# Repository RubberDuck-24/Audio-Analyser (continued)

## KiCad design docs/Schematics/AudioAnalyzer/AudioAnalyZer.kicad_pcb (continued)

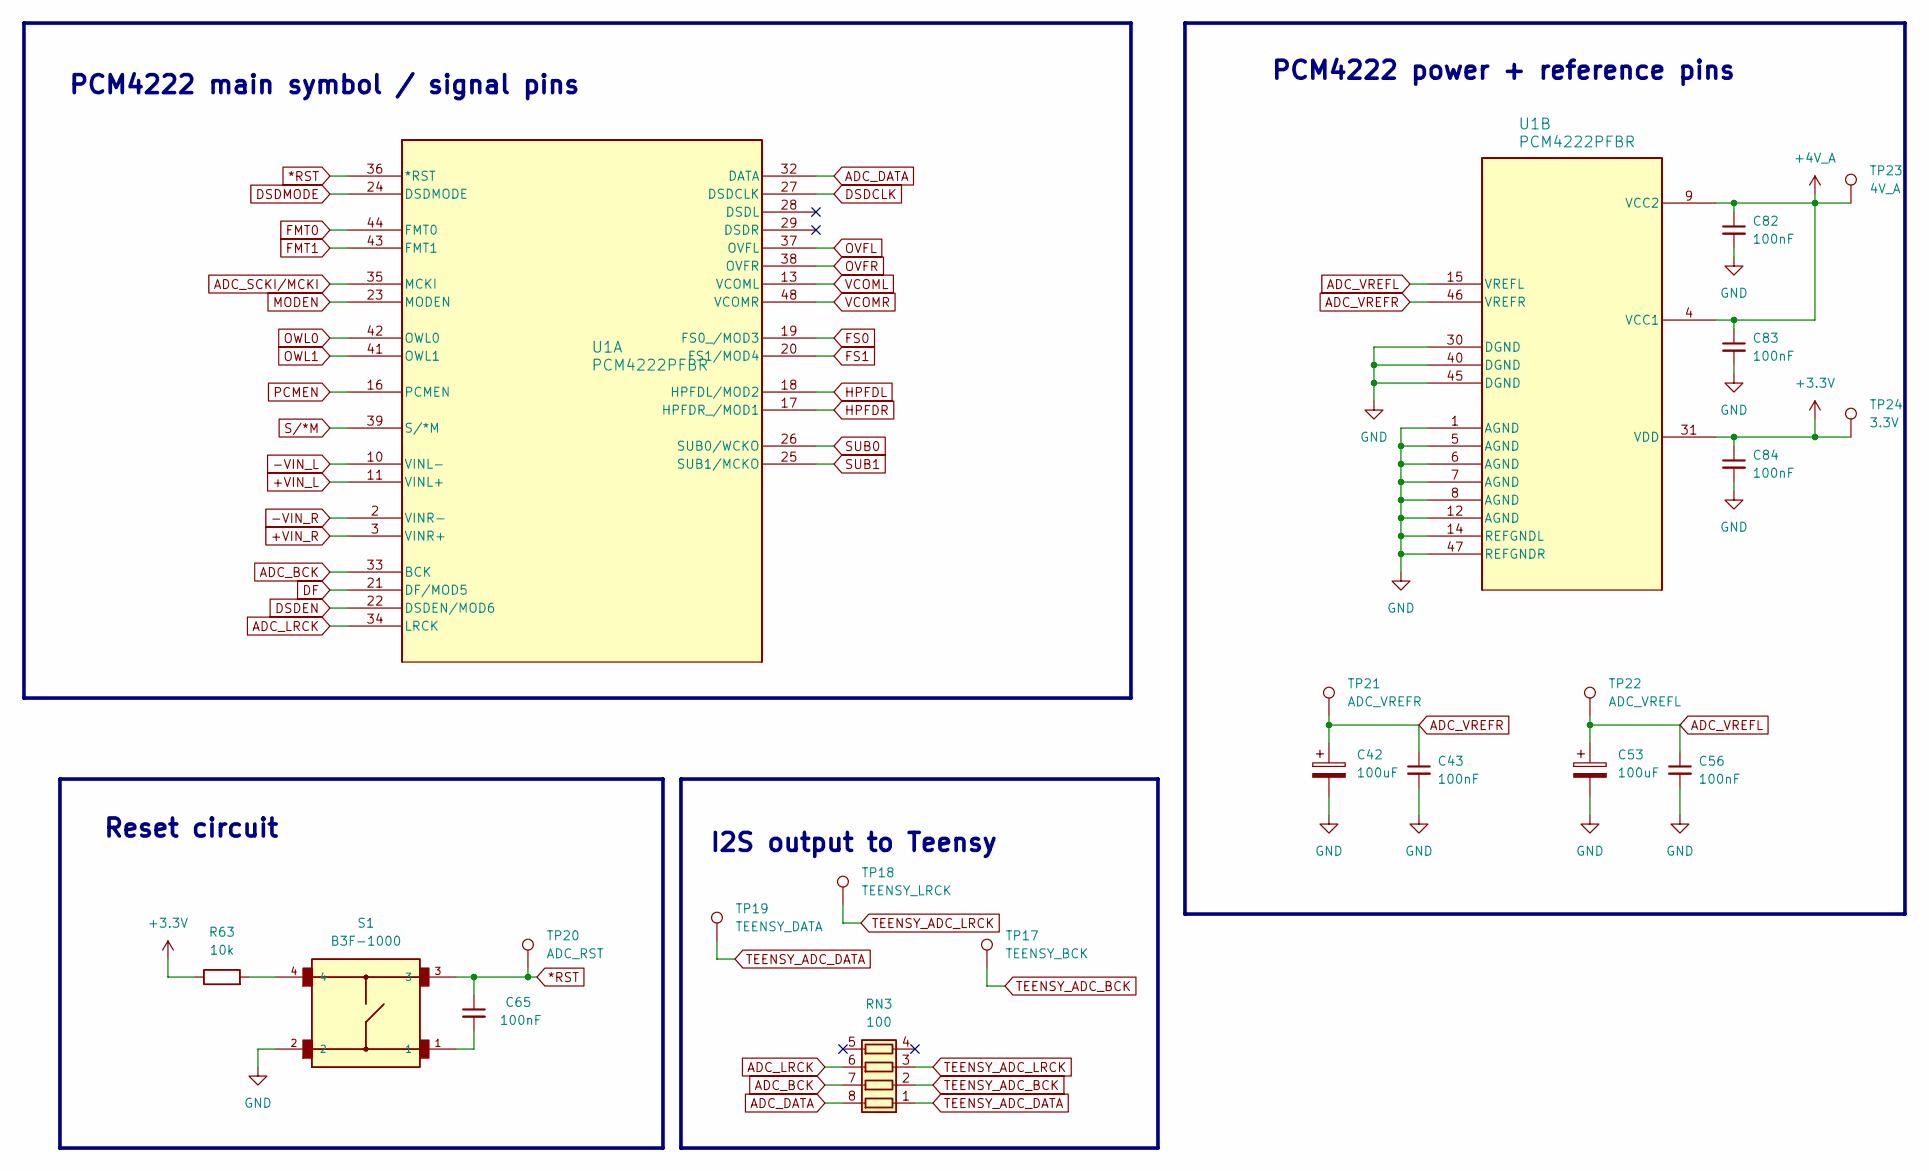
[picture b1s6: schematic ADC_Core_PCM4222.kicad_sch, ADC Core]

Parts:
C42, C53: 100uF; C_1210_3225Metric
C43, C56, C65, C82, C83, C84: 100nF; C_0603_1608Metric_Pad1.08x0.95mm_HandSolder
R63: 10k; R_0603_1608Metric_Pad0.98x0.95mm_HandSolder
RN3: 100; RESCAXS80P320X160X60-8N
S1: B3F-1000; SW_B3F-1000
TP17: TEENSY_BCK; TestPoint_Pad_D1.5mm
TP18: TEENSY_LRCK; TestPoint_Pad_D1.5mm
TP19: TEENSY_DATA; TestPoint_Pad_D1.5mm
TP20: ADC_RST; TestPoint_Pad_D1.5mm
TP21: ADC_VREFR; TestPoint_Pad_D1.5mm
TP22: ADC_VREFL; TestPoint_Pad_D1.5mm
TP23: 4V_A; TestPoint_Pad_D1.5mm
TP24: 3.3V; TestPoint_Pad_D1.5mm
U1: PCM4222PFBR; PFB48-M

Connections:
*RST: C65.1, S1.3, TP20.1 (1_1), U1.36 (*RST)
+3.3V: C84.1, R63.1, TP24.1 (1_1), U1.31 (VDD); also elsewhere on the board
+4V_A: C82.1, C83.1, TP23.1, U1.4 (VCC1), U1.9 (VCC2); also elsewhere on the board
+VIN_L: U1.11 (VINL+); also elsewhere on the board
+VIN_R: U1.3 (VINR+); also elsewhere on the board
-VIN_L: U1.10 (VINL-); also elsewhere on the board
-VIN_R: U1.2 (VINR-); also elsewhere on the board
ADC_BCK: RN3.7 (R2.2), U1.33 (BCK); also elsewhere on the board
ADC_DATA: RN3.8 (R1.2), U1.32 (DATA)
ADC_LRCK: RN3.6 (R3.2), U1.34 (LRCK); also elsewhere on the board
ADC_SCKI/MCKI: U1.35 (MCKI); also elsewhere on the board
ADC_VREFL: C53.1, C56.1, TP22.1 (1_1), U1.15 (VREFL)
ADC_VREFR: C42.1, C43.1, TP21.1 (1_1), U1.46 (VREFR)
DF: U1.21 (DF/MOD5); also elsewhere on the board
DSDCLK: U1.27 (DSDCLK)
DSDEN: U1.22 (DSDEN/MOD6); also elsewhere on the board
DSDMODE: U1.24 (DSDMODE); also elsewhere on the board
FMT0: U1.44 (FMT0); also elsewhere on the board
FMT1: U1.43 (FMT1); also elsewhere on the board
FS0: U1.19 (FS0_/MOD3); also elsewhere on the board
FS1: U1.20 (FS1/MOD4); also elsewhere on the board
GND: C42.2, C43.2, C53.2, C56.2, C82.2, C83.2, C84.2, S1.2, U1.1 (AGND), U1.5 (AGND), U1.6 (AGND), U1.7 (AGND), U1.8 (AGND), U1.12 (AGND), U1.14 (REFGNDL), U1.30 (DGND), U1.40 (DGND), U1.45 (DGND), U1.47 (REFGNDR); also elsewhere on the board
HPFDL: U1.17 (HPFDR_/MOD1), U1.18 (HPFDL/MOD2); also elsewhere on the board
MODEN: U1.23 (MODEN); also elsewhere on the board
unnamed: C65.2, S1.1
unnamed: R63.2, S1.4
OVFL: U1.37 (OVFL); also elsewhere on the board
OVFR: U1.38 (OVFR); also elsewhere on the board
OWL0: U1.42 (OWL0); also elsewhere on the board
OWL1: U1.41 (OWL1); also elsewhere on the board
PCMEN: U1.16 (PCMEN); also elsewhere on the board
SUB0: U1.26 (SUB0/WCKO); also elsewhere on the board
SUB1: U1.25 (SUB1/MCKO); also elsewhere on the board
S/*M: U1.39 (S/*M); also elsewhere on the board
TEENSY_ADC_BCK: RN3.2 (R2.1), TP17.1 (1_1); also elsewhere on the board
TEENSY_ADC_DATA: RN3.1 (R1.1), TP19.1 (1_1); also elsewhere on the board
TEENSY_ADC_LRCK: RN3.3 (R3.1), TP18.1 (1_1); also elsewhere on the board
VCOML: U1.13 (VCOML); also elsewhere on the board
VCOMR: U1.48 (VCOMR); also elsewhere on the board

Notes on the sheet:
PCM4222 main symbol / signal pins
I2S output to Teensy
PCM4222 power + reference pins
Reset circuit

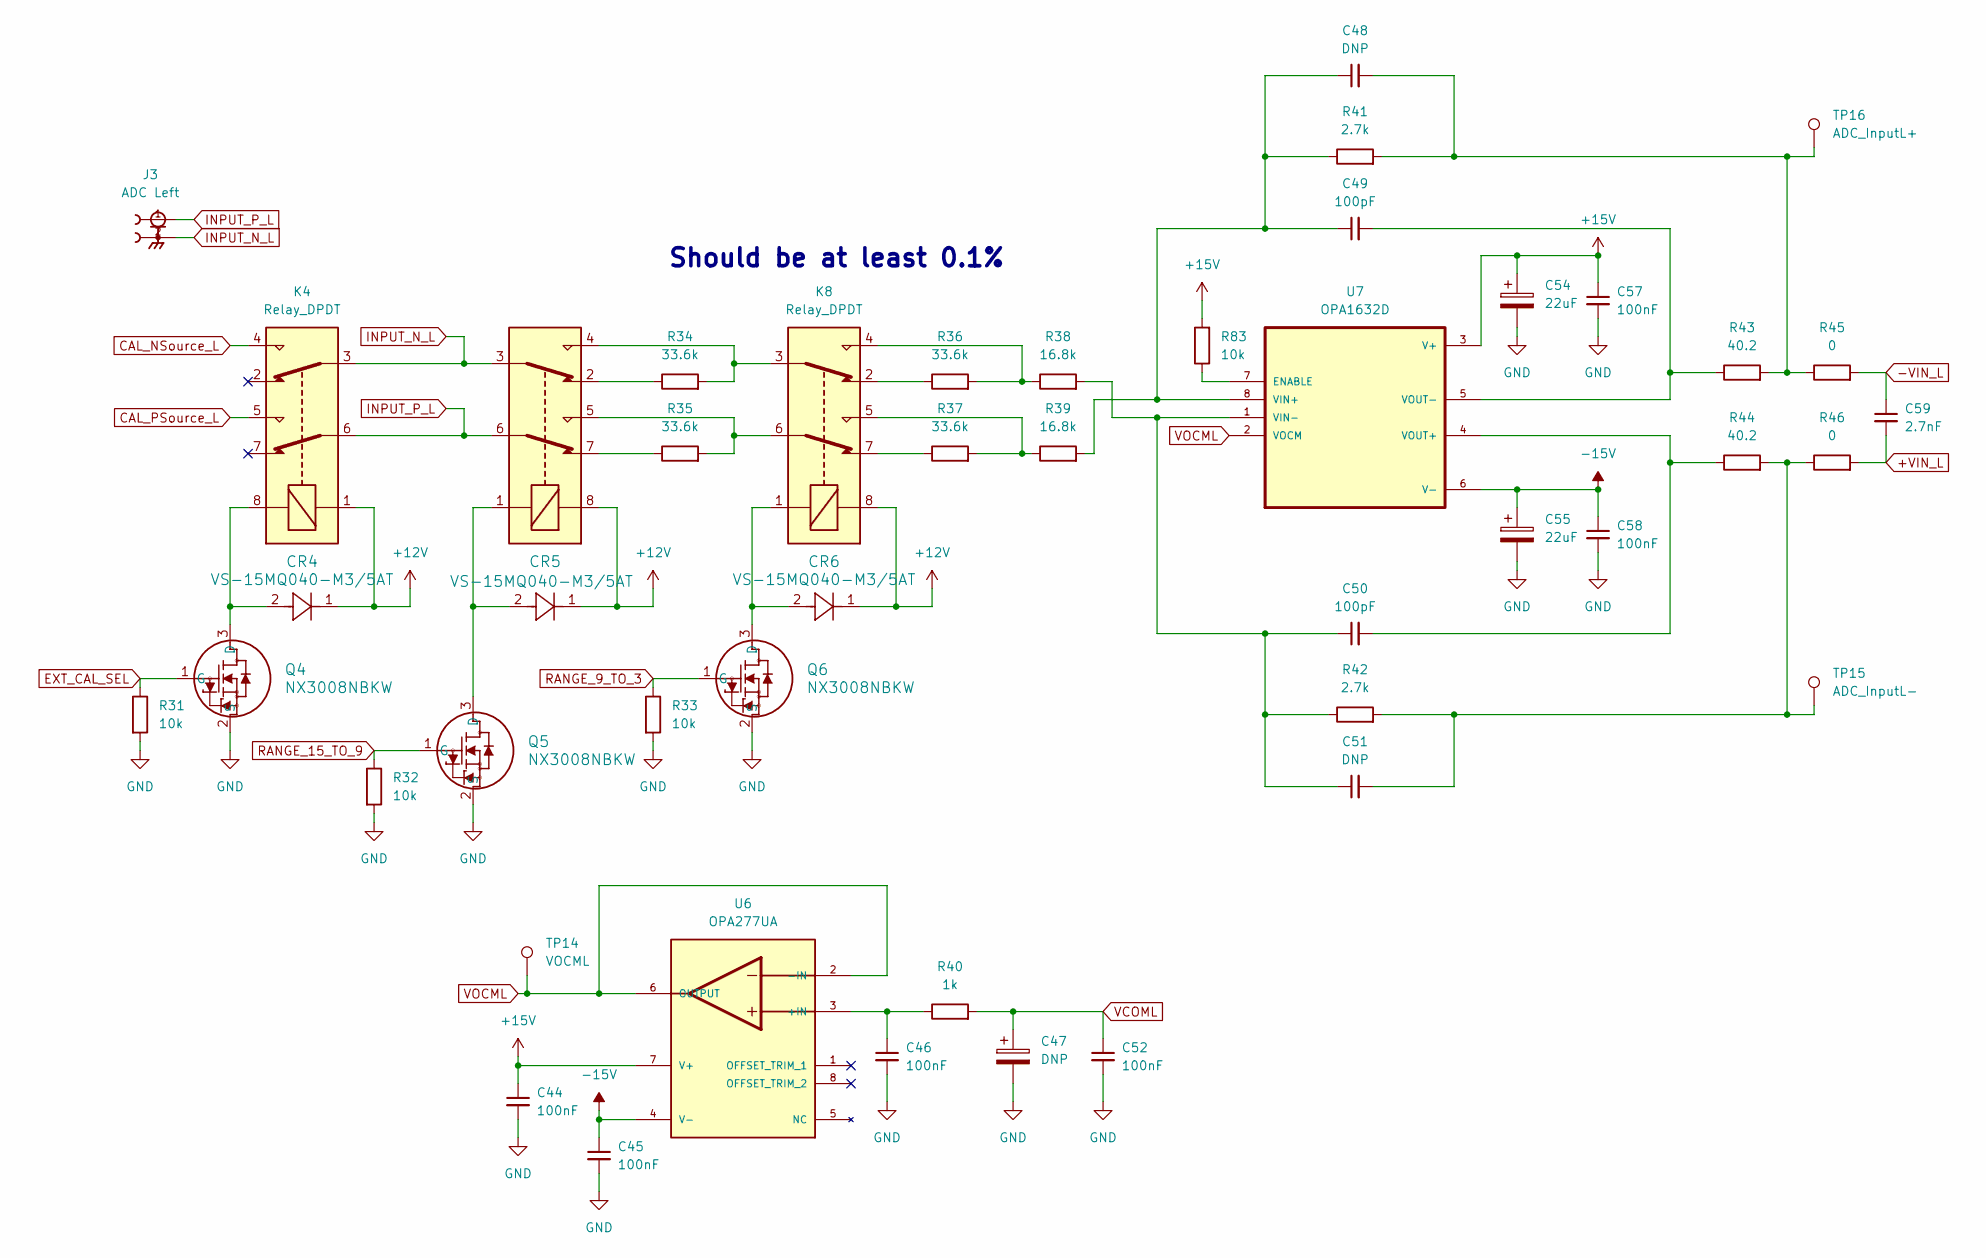
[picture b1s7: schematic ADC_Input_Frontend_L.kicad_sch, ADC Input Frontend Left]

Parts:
C44, C45, C46, C52, C57, C58: 100nF; C_0603_1608Metric_Pad1.08x0.95mm_HandSolder
C47, C48, C51: DNP; C_0603_1608Metric_Pad1.08x0.95mm_HandSolder
C49, C50: 100pF; C_0603_1608Metric_Pad1.08x0.95mm_HandSolder
C54, C55: 22uF; C_1206_3216Metric
C59: 2.7nF; C_0603_1608Metric_Pad1.08x0.95mm_HandSolder
CR4, CR5, CR6: VS-15MQ040-M3/5AT; CR_Q040-M3&slash_5AT_VIS
J3: ADC Left; LINX_CONBNC002
K4, K7, K8: Relay_DPDT; RELAY_IM06DGR
Q4, Q5, Q6: NX3008NBKW; SC-70_SOT323_NEX
R31, R32, R33, R83: 10k; R_0603_1608Metric_Pad0.98x0.95mm_HandSolder
R34, R35, R36, R37: 33.6k; R_0603_1608Metric_Pad0.98x0.95mm_HandSolder
R38, R39: 16.8k; R_0603_1608Metric_Pad0.98x0.95mm_HandSolder
R40: 1k; R_0603_1608Metric_Pad0.98x0.95mm_HandSolder
R41, R42: 2.7k; R_0603_1608Metric_Pad0.98x0.95mm_HandSolder
R43, R44: 40.2; R_0603_1608Metric_Pad0.98x0.95mm_HandSolder
R45, R46: 0; R_0603_1608Metric_Pad0.98x0.95mm_HandSolder
TP14: VOCML; TestPoint_Pad_D1.5mm
TP15: ADC_InputL-; TestPoint_Pad_D1.5mm
TP16: ADC_InputL+; TestPoint_Pad_D1.5mm
U6: OPA277UA; SOIC127P599X175-8N; PARTREV 02/2019
U7: OPA1632D; SOIC127P599X175-8N

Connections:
+12V: CR4.1, CR5.1, CR6.1, K4.1, K7.8, K8.8; also elsewhere on the board
+15V: C44.1, C54.1, C57.1, R83.2, U6.7 (V+), U7.3 (V+); also elsewhere on the board
+VIN_L: C59.2, R46.2; also elsewhere on the board
-15V: C45.1, C55.1, C58.1, U6.4 (V-), U7.6 (V-); also elsewhere on the board
-VIN_L: C59.1, R45.2; also elsewhere on the board
CAL_NSource_L: K4.4; also elsewhere on the board
CAL_PSource_L: K4.5; also elsewhere on the board
EXT_CAL_SEL: Q4.1 (G), R31.1; also elsewhere on the board
GND: C44.2, C45.2, C46.2, C47.2, C52.2, C54.2, C55.2, C57.2, C58.2, Q4.2 (S), Q5.2 (S), Q6.2 (S), R31.2, R32.2, R33.2; also elsewhere on the board
INPUT_N_L: J3.2, J3.S1, J3.S2, K4.3, K7.3
INPUT_P_L: J3.1, K4.6, K7.6
unnamed: C48.2, R41.2, R43.2, R45.1, TP16.1 (1_1)
unnamed: C51.2, R42.2, R44.2, R46.1, TP15.1 (1_1)
unnamed: K7.2, R34.1
unnamed: K7.4, K8.3, R34.2
unnamed: K7.5, K8.6, R35.2
unnamed: K7.7, R35.1
unnamed: K8.2, R36.1
unnamed: K8.4, R36.2, R38.1
unnamed: K8.5, R37.2, R39.1
unnamed: K8.7, R37.1
unnamed: CR4.2, K4.8, Q4.3 (D)
unnamed: CR5.2, K7.1, Q5.3 (D)
unnamed: CR6.2, K8.1, Q6.3 (D)
unnamed: C46.1, R40.1, U6.3 (+IN)
unnamed: R83.1, U7.7 (ENABLE)
unnamed: C48.1, C49.1, R39.2, R41.1, U7.8 (VIN+)
unnamed: C50.1, C51.1, R38.2, R42.1, U7.1 (VIN-)
unnamed: C50.2, R44.1, U7.4 (VOUT+)
unnamed: C49.2, R43.1, U7.5 (VOUT-)
RANGE_9_TO_3: Q6.1 (G), R33.1; also elsewhere on the board
RANGE_15_TO_9: Q5.1 (G), R32.1; also elsewhere on the board
VCOML: C47.1, C52.1, R40.2; also elsewhere on the board
VOCML: TP14.1 (1_1), U6.2 (-IN), U6.6 (OUTPUT), U7.2 (VOCM)

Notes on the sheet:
Should be at least 0.1%

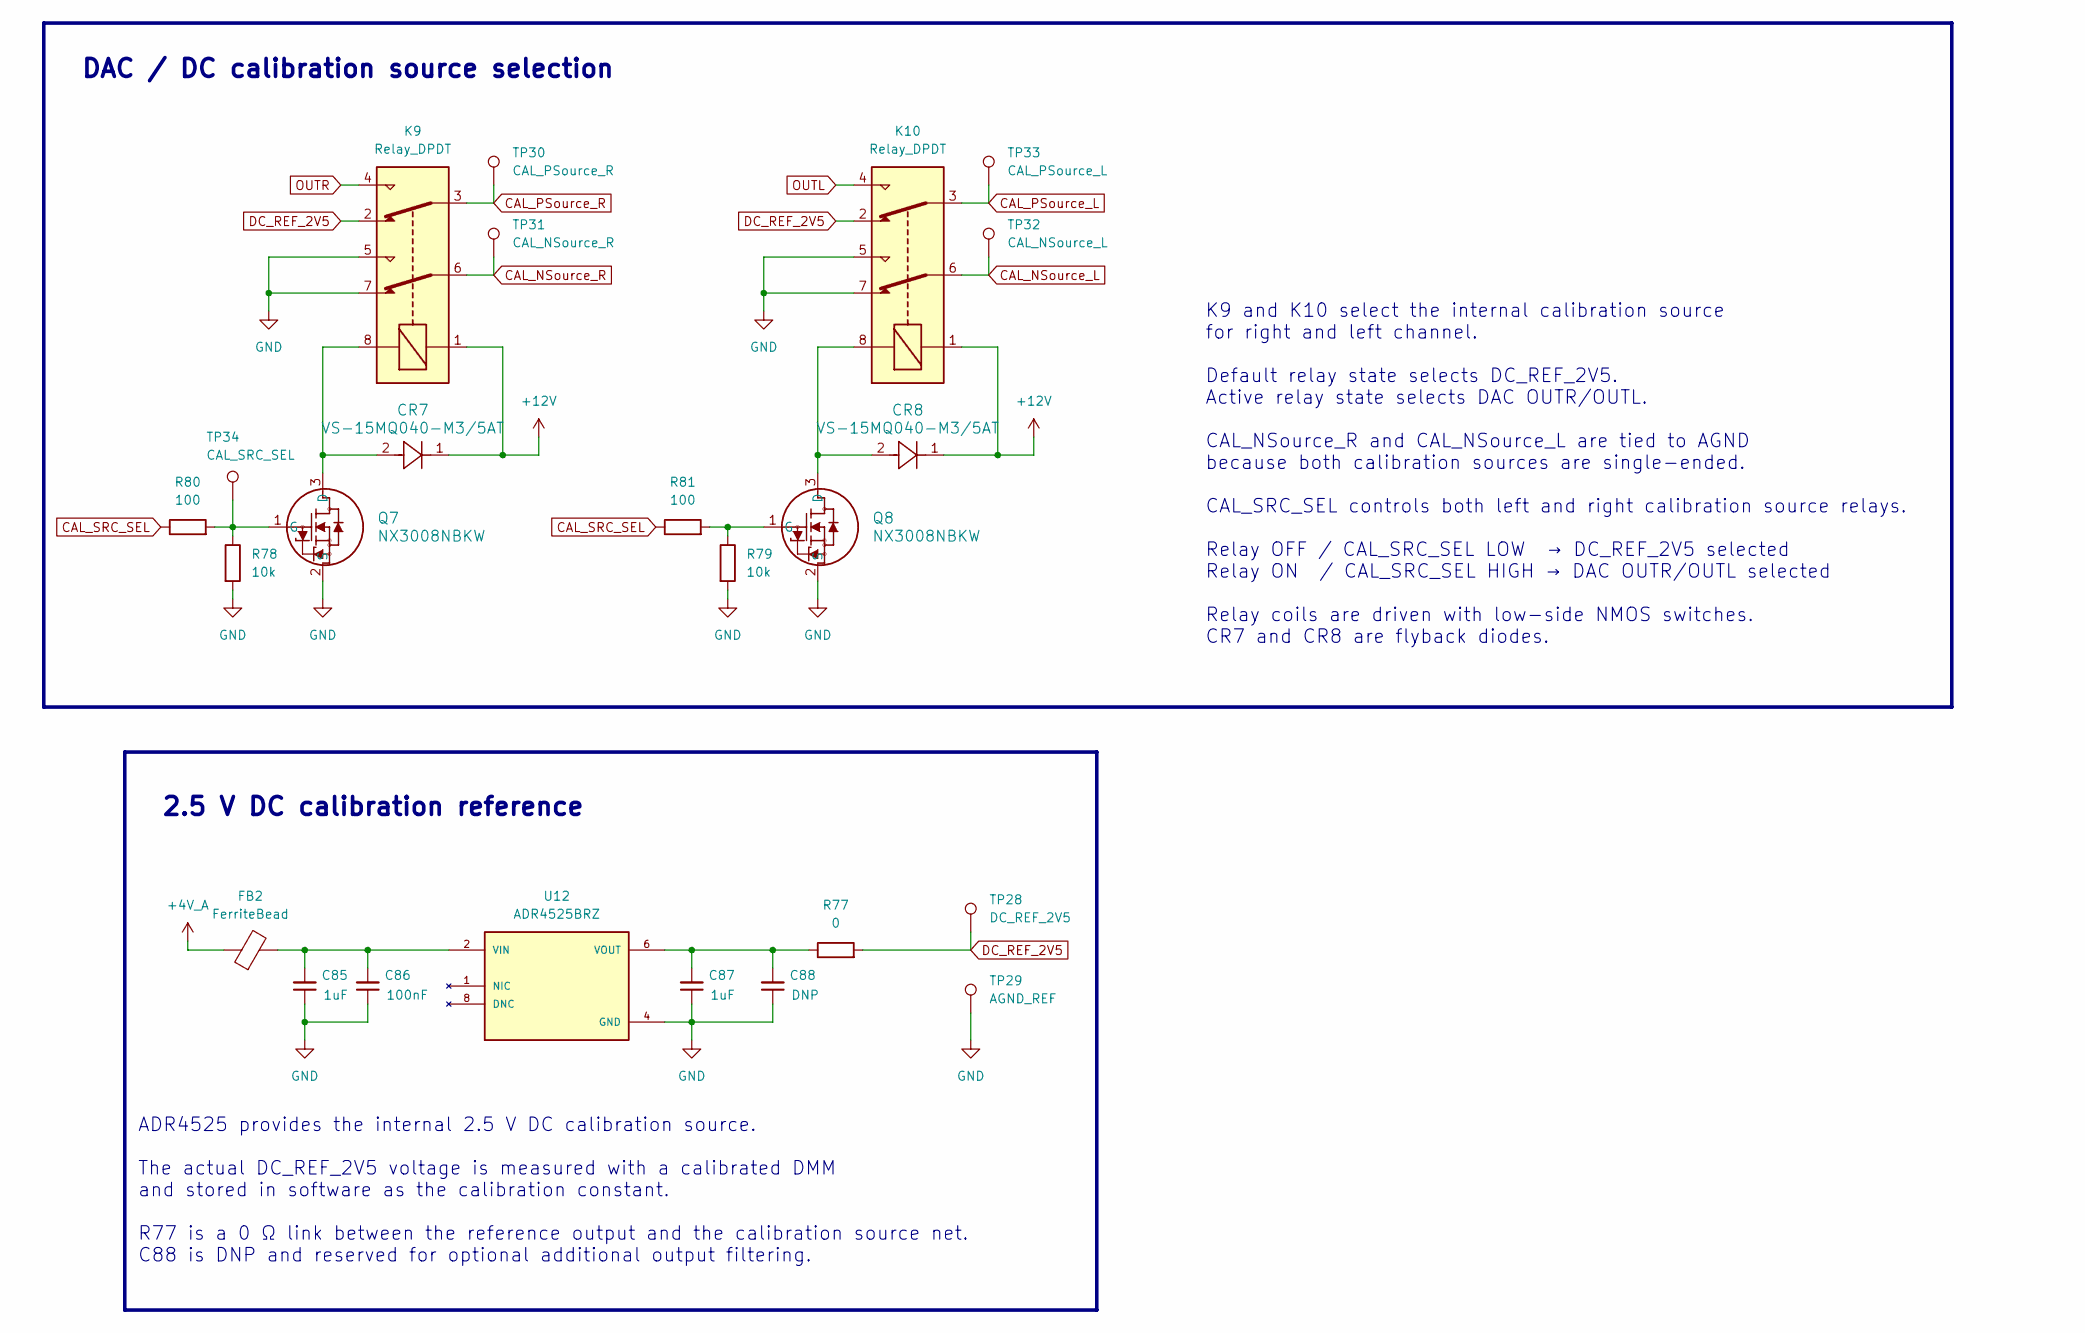
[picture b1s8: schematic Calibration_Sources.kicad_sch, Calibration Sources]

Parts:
C85, C87: 1uF; C_0603_1608Metric_Pad1.08x0.95mm_HandSolder
C86: 100nF; C_0603_1608Metric_Pad1.08x0.95mm_HandSolder
C88: DNP; C_0603_1608Metric_Pad1.08x0.95mm_HandSolder
CR7, CR8: VS-15MQ040-M3/5AT; CR_Q040-M3&slash_5AT_VIS
FB2: FerriteBead; BEADC2012X105N
K9, K10: Relay_DPDT; RELAY_IM06DGR
Q7, Q8: NX3008NBKW; SC-70_SOT323_NEX
R77: 0; R_0603_1608Metric_Pad0.98x0.95mm_HandSolder
R78, R79: 10k; R_0603_1608Metric_Pad0.98x0.95mm_HandSolder
R80, R81: 100; R_0603_1608Metric_Pad0.98x0.95mm_HandSolder
TP28: DC_REF_2V5; TestPoint_Pad_D1.5mm
TP29: AGND_REF; TestPoint_Pad_D1.5mm
TP30: CAL_PSource_R; TestPoint_Pad_D1.5mm
TP31: CAL_NSource_R; TestPoint_Pad_D1.5mm
TP32: CAL_NSource_L; TestPoint_Pad_D1.5mm
TP33: CAL_PSource_L; TestPoint_Pad_D1.5mm
TP34: CAL_SRC_SEL; TestPoint_Pad_D1.5mm
U12: ADR4525BRZ; SOIC127P600X175-8N; PARTREV G

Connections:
+4V_A: FB2.1; also elsewhere on the board
+12V: CR7.1, CR8.1, K9.1, K10.1; also elsewhere on the board
CAL_NSource_L: K10.6, TP32.1 (1_1); also elsewhere on the board
CAL_NSource_R: K9.6, TP31.1 (1_1); also elsewhere on the board
CAL_PSource_L: K10.3, TP33.1 (1_1); also elsewhere on the board
CAL_PSource_R: K9.3, TP30.1 (1_1); also elsewhere on the board
CAL_SRC_SEL: R80.1, R81.1; also elsewhere on the board
DC_REF_2V5: K9.2, K10.2, R77.2, TP28.1 (1_1)
GND: C85.1, C86.1, C87.1, C88.1, K9.5, K9.7, K10.5, K10.7, Q7.2 (S), Q8.2 (S), R78.2, R79.2, TP29.1 (1_1), U12.4 (GND); also elsewhere on the board
unnamed: CR7.2, K9.8, Q7.3 (D)
unnamed: Q7.1 (G), R78.1, R80.2, TP34.1 (1_1)
unnamed: CR8.2, K10.8, Q8.3 (D)
unnamed: Q8.1 (G), R79.1, R81.2
unnamed: C85.2, C86.2, FB2.2, U12.2 (VIN)
unnamed: C87.2, C88.2, R77.1, U12.6 (VOUT)
OUTL: K10.4; also elsewhere on the board
OUTR: K9.4; also elsewhere on the board

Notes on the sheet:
K9 and K10 select the internal calibration source for right and left channel. Default relay state selects DC_REF_2V5. Active relay state selects DAC OUTR/OUTL. CAL_NSource_R and CAL_NSource_L are tied to AGND because both calibration sources are single-ended. CAL_SRC_SEL controls both left and righ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
ADR4525 provides the internal 2.5 V DC calibration source. The actual DC_REF_2V5 voltage is measured with a calibrated DMM and stored in software as the calibration constant. R77 is a 0 Ω link between the reference output and the calibration source net. C88 is DNP and reserved for optional addition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
DAC / DC calibration source selection
2.5 V DC calibration reference

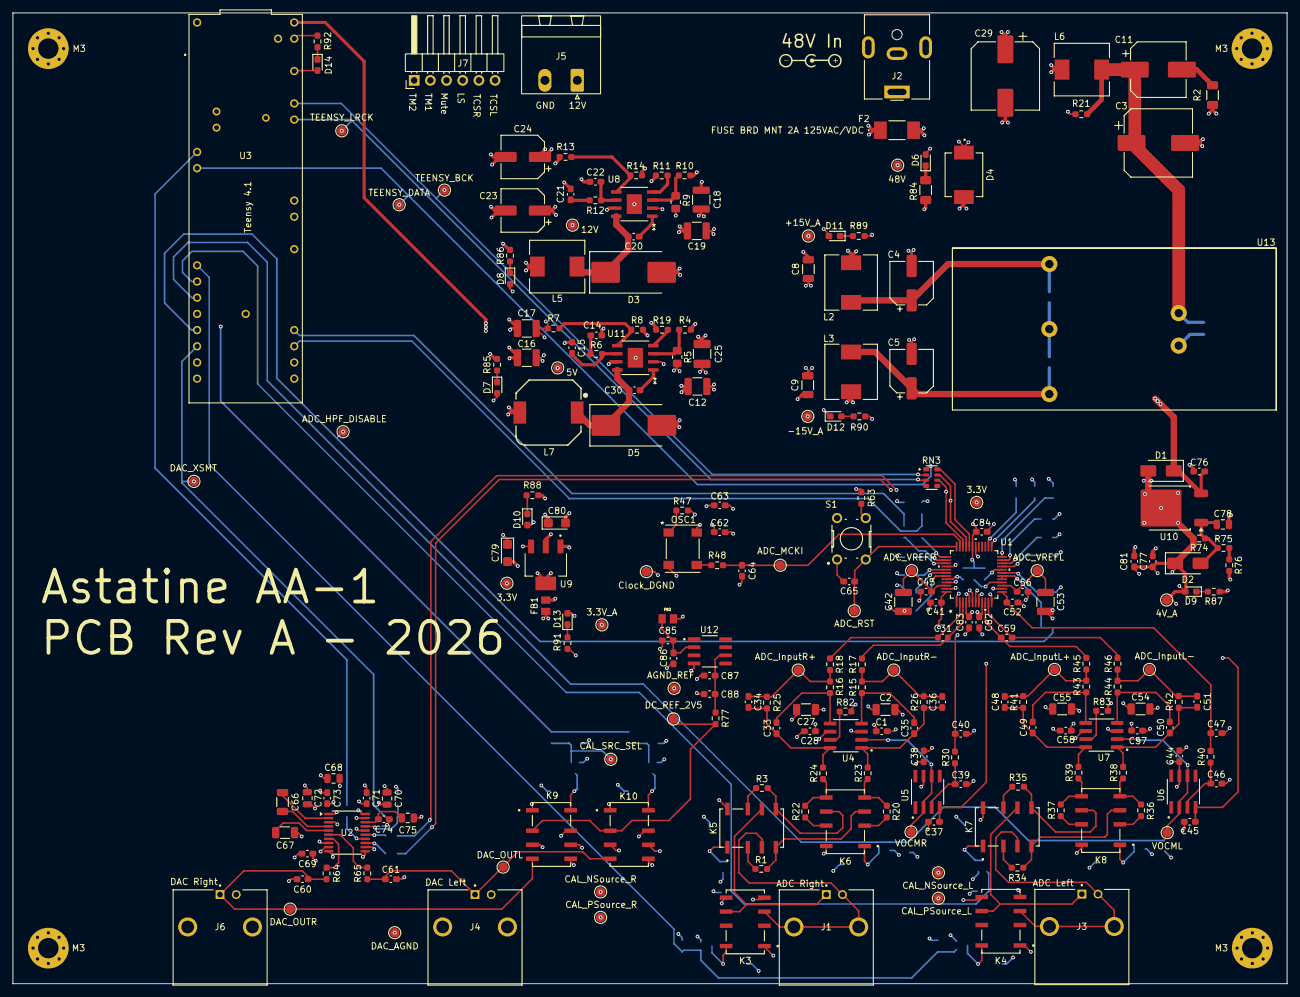
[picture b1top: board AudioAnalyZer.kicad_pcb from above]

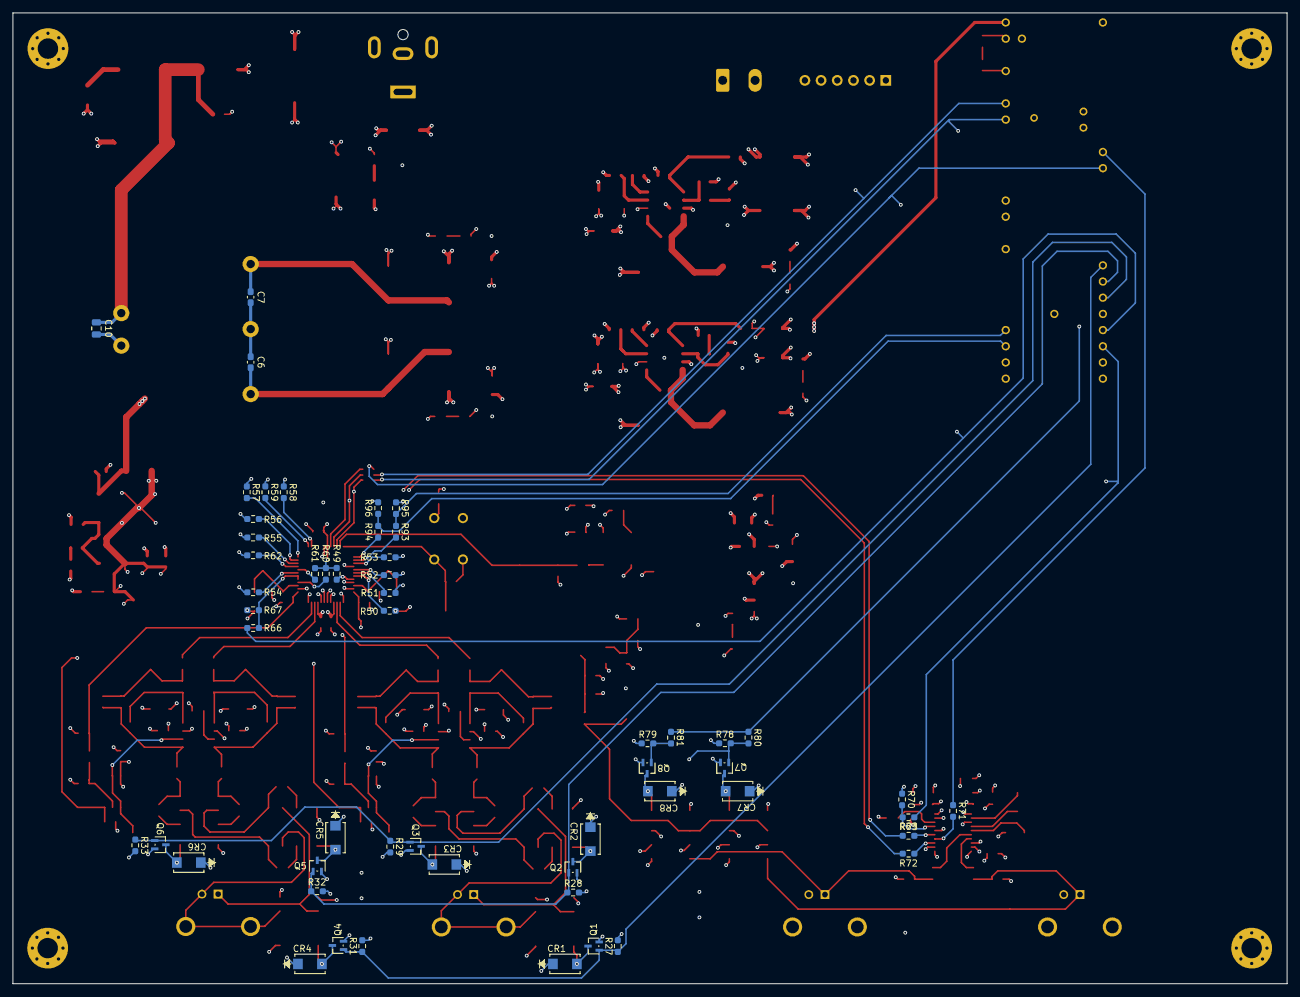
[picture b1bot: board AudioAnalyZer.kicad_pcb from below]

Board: 4 copper layers, 199.9 x 152.3 mm, 288 parts (54 on the bottom side), 159 nets.

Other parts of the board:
M3, M3#2, M3#3, M3#4: MountingHole_3.2mm_M3_Pad_Via

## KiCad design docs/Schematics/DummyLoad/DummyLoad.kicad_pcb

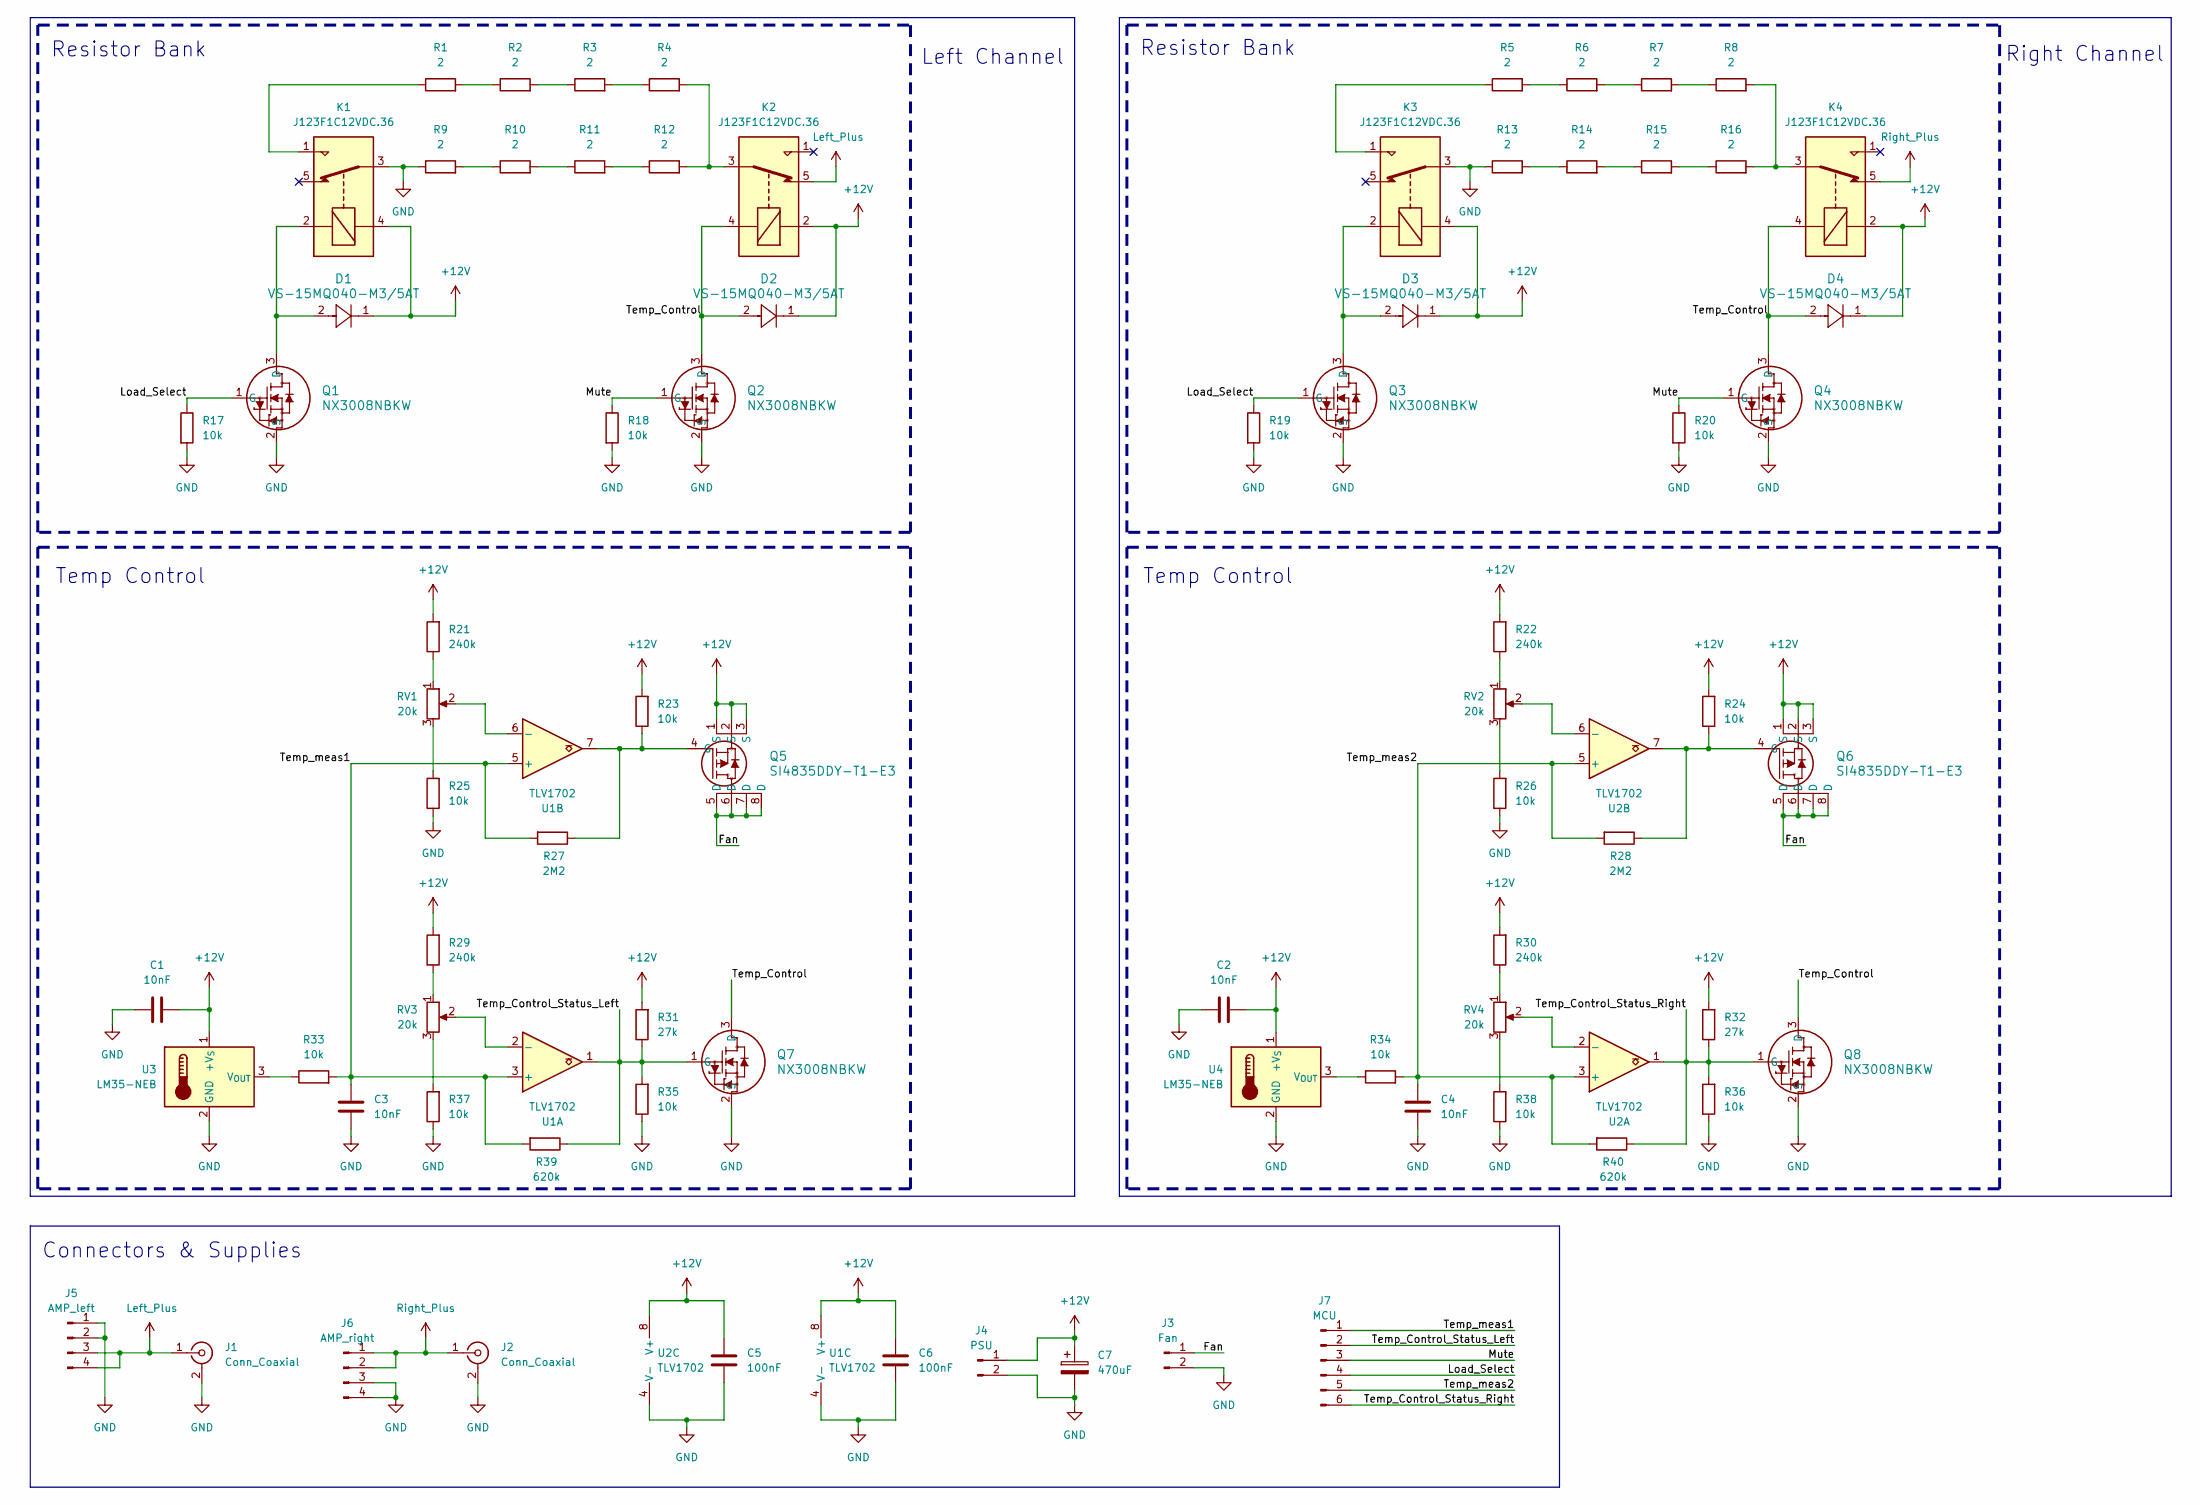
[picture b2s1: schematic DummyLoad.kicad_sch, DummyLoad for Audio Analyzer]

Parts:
C1, C2, C3, C4: 10nF; C_0603_1608Metric_Pad1.08x0.95mm_HandSolder
C5, C6: 100nF; C_0603_1608Metric_Pad1.08x0.95mm_HandSolder
C7: 470uF; CP_Radial_D10.0mm_P5.00mm
D1, D2, D3, D4: VS-15MQ040-M3/5AT; CR_Q040-M3&slash_5AT_VIS
J1, J2: Conn_Coaxial; LINX_CONBNC002
J3: Fan; PhoenixContact_MSTBA_2,5_2-G-5,08_1x02_P5.08mm_Horizontal
J4: PSU; PhoenixContact_MSTBA_2,5_2-G-5,08_1x02_P5.08mm_Horizontal
J5: AMP_left; PhoenixContact_MSTBA_2,5_4-G-5,08_1x04_P5.08mm_Horizontal
J6: AMP_right; PhoenixContact_MSTBA_2,5_4-G-5,08_1x04_P5.08mm_Horizontal
J7: MCU; PinHeader_1x06_P2.54mm_Vertical
K1, K2, K3, K4: J123F1C12VDC.36; RELAY5_J123F1C5VDC.36_CRS
Q1, Q2, Q3, Q4, Q7, Q8: NX3008NBKW; SC-70_SOT323_NEX
Q5, Q6: SI4835DDY-T1-E3; SOIC_5DDY-T1-E3_VIS
R1, R2, R3, R4, R5, R6, R7, R8, R9, R10, R11, R12, R13, R14, R15, R16: 2; LTO100_VIS
R17, R18, R19, R20, R23, R24, R25, R26, R33, R34, R35, R36, R37, R38: 10k; R_0603_1608Metric_Pad0.98x0.95mm_HandSolder
R21, R22, R29, R30: 240k; R_0603_1608Metric_Pad0.98x0.95mm_HandSolder
R27, R28: 2M2; R_0603_1608Metric_Pad0.98x0.95mm_HandSolder
R31, R32: 27k; R_0603_1608Metric_Pad0.98x0.95mm_HandSolder
R39, R40: 620k; R_0603_1608Metric_Pad0.98x0.95mm_HandSolder
RV1, RV2, RV3, RV4: 20k; Potentiometer_Bourns_3296Y_Vertical
U1, U2: TLV1702; DGK8_TEX-M
U3, U4: LM35-NEB; TO-220-3_Vertical

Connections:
+12V: C1.2, C2.2, C5.2, C6.2, C7.1, D1.1, D2.1, D3.1, D4.1, J4.1, K1.4, K2.2, K3.4, K4.2, Q5.1 (S), Q5.2 (S), Q5.3 (S), Q6.1 (S), Q6.2 (S), Q6.3 (S), R21.2, R22.2, R23.2, R24.2, R29.2, R30.2, R31.2, R32.2, U1.8 (V+), U2.8 (V+), U3.1 (+V_{S}), U4.1 (+V_{S})
/Fan: J3.1, Q5.5 (D), Q5.6 (D), Q5.7 (D), Q5.8 (D), Q6.5 (D), Q6.6 (D), Q6.7 (D), Q6.8 (D)
/Load_Select: J7.4, Q1.1 (G), Q3.1 (G), R17.1, R19.1
/Mute: J7.3, Q2.1 (G), Q4.1 (G), R18.1, R20.1
/Temp_Control: D2.2, D4.2, K2.4, K4.4, Q2.3 (D), Q4.3 (D), Q7.3 (D), Q8.3 (D)
/Temp_Control_Status_Left: J7.2, Q7.1 (G), R31.1, R35.2, R39.1, U1.1
/Temp_Control_Status_Right: J7.6, Q8.1 (G), R32.1, R36.2, R40.1, U2.1
/Temp_meas1: C3.2, J7.1, R27.2, R33.2, R39.2, U1.3 (+), U1.5 (+)
/Temp_meas2: C4.2, J7.5, R28.2, R34.2, R40.2, U2.3 (+), U2.5 (+)
GND: C1.1, C2.1, C3.1, C4.1, C5.1, C6.1, C7.2, J1.2 (Ext), J2.2 (Ext), J3.2, J4.2, J5.1, J5.2, J6.3, J6.4, K1.3, K3.3, Q1.2 (S), Q2.2 (S), Q3.2 (S), Q4.2 (S), Q7.2 (S), Q8.2 (S), R9.1, R13.1, R17.2, R18.2, R19.2, R20.2, R25.1, R26.1, R35.1, R36.1, R37.1, R38.1, U1.4 (V-), U2.4 (V-), U3.2 (GND), U4.2 (GND)
Left_Plus: J1.1 (In), J5.3, J5.4, K2.5
unnamed: K1.1, R1.1
unnamed: K2.3, R4.2, R12.2
unnamed: K3.1, R5.1
unnamed: K4.3, R8.2, R16.2
unnamed: D1.2, K1.2, Q1.3 (D)
unnamed: D3.2, K3.2, Q3.3 (D)
unnamed: Q5.4 (G), R23.1, R27.1, U1.7
unnamed: Q6.4 (G), R24.1, R28.1, U2.7
unnamed: R1.2, R2.1
unnamed: R2.2, R3.1
unnamed: R3.2, R4.1
unnamed: R5.2, R6.1
unnamed: R6.2, R7.1
unnamed: R7.2, R8.1
unnamed: R9.2, R10.1
unnamed: R10.2, R11.1
unnamed: R11.2, R12.1
unnamed: R13.2, R14.1
unnamed: R14.2, R15.1
unnamed: R15.2, R16.1
unnamed: R21.1, RV1.1
unnamed: R22.1, RV2.1
unnamed: R25.2, RV1.3
unnamed: R26.2, RV2.3
unnamed: R29.1, RV3.1
unnamed: R30.1, RV4.1
unnamed: R37.2, RV3.3
unnamed: R38.2, RV4.3
unnamed: RV3.2, U1.2 (-)
unnamed: RV1.2, U1.6 (-)
unnamed: RV4.2, U2.2 (-)
unnamed: RV2.2, U2.6 (-)
unnamed: R33.1, U3.3 (V_{OUT})
unnamed: R34.1, U4.3 (V_{OUT})
Right_Plus: J2.1 (In), J6.1, J6.2, K4.5

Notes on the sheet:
Right Channel
Connectors & Supplies
Resistor Bank
Left Channel
Temp Control

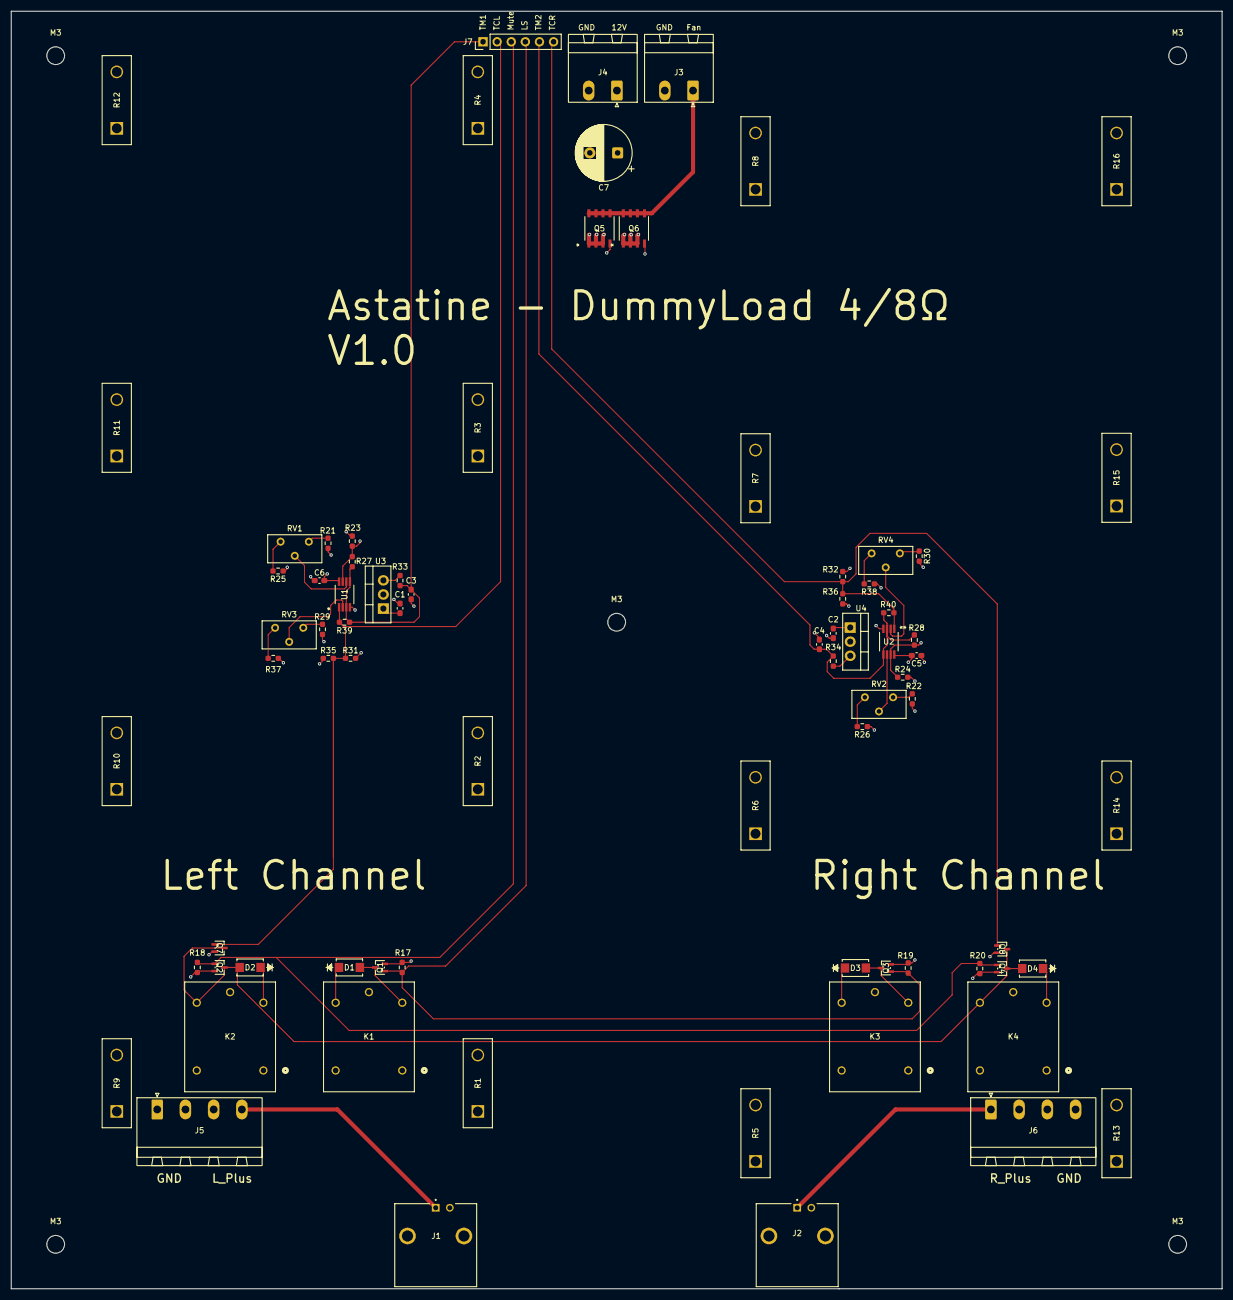
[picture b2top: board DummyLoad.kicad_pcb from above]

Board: 4 copper layers, 218.0 x 230.0 mm, 83 parts (0 on the bottom side), 46 nets.

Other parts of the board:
M3, M3#2, M3#3, M3#4, M3#5: MountingHole_3.2mm_M3

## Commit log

2026-03-04 Initial commit: PlatformIO Teensy 4.1 hello world
2026-03-07 Add I2S slave firmware and Python serial multimeter
    - firmware: Teensy 4.1 I2S slave RX, CSV streaming til PC
    - software: RMS multimeter med dBFS visning og auto COM-detect
2026-03-18 New python code for debugging and for visual view
2026-04-17 Changed from Altium to KiCad do to licens issues, and have designed 1st revision of the DummyLoad
2026-04-17 A more updated README
2026-04-17 adding the folder pictures
2026-04-17 Add block diagram to README
2026-04-17 Add block diagram image
2026-04-17 Fix image path capitalisation
2026-04-22 Version 1.0 of the DummyLoad
2026-04-22 Updated python tools for testing the connection between the pc, teensy and ADC
2026-04-23 Updated firmware for teensy, with DAC setup
2026-05-15 Version 1.0 of the audio analyzer and fix embedded repo warnings
